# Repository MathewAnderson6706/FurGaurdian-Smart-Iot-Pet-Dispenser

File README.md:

# Automatic Pet Food Dispensor using RasperryPi 4 
Title Page (1st odd page not numbered, X.0 sections begin on odd pages, otherwise double sided and numbered)  
## Declaration of Joint Authorship   
### Task Distribution
We, FurGuardian, confirm that this breakdown of authorship represents my contribution to the work submitted for assessment and my contribution is my own work and  is expressed in my own words. Any uses made within the Technology Report of the works of any other author, separate to the work group, in any form (ideas, equations, figures, texts, tables, programs), are properly acknowledged at the point of use. A list of the references used is included.
| Task                  | Mathew | Justin | Tevadi | Zane |
|-----------------------|--------|--------|--------|------|
| **3D Print / Container**   | 50%   | 10%   | 10%   | 30%  |
| **Mobile Programming**     | 30%   | 50%   | 10%   | 10%  |
| **Hardware Connectivity**  | 45%   | 25%   | 15%   | 15%  |
| **Hardware Programming**   | 40%   | 40%   | 10%   | 10%  |
| **Documentation**          | 25%   | 25%   | 25%   | 25%  |

[^1]
[^1]: Technology Report Guidelines. OACETT, Revised September 2022. Available at: https://www.oacett.org/getmedia/5ad707d7-f472-4b24-a7fe-f34e270b0c41/2022_TR_Guidelines_-_Updated_Version_-_Sept_2022.pdf
## Proposal/Project Specifications   
[Link to proposal](wk01proposal.md).   
## Executive Summary   
Our project focuses on enhancing pet care for owners who are away during the day. It features a **smart pet food dispenser** equipped with advanced functionalities:

- **Camera**:  
  Allow owners to interact with their pets remotely, ensuring constant connection and engagement.

- **Infrared Sensor**:  
  Detects pet presence to automate feeding and interaction processes.

- **Stepper Motor**:  
  Dispenses precise portions of food to maintain proper dietary control.

- **solenoid push intermittent**:  
  Enables treat dispensing as an added feature for rewarding and engaging pets.

## Table of Contents

[Declaration of Joint Authorship](#declaration-of-joint-authorship)   
[Proposal/Project Specifications](#proposalproject-specifications)   
[Executive Summary](#executive-summary)   
[Table of Contents](#table-of-contents)   
[List of Figures](#list-of-figures)   

[1.0 Introduction](#10-introduction)   
[1.1 Background](#11-background)   
[1.2 Project Requirements and Specifications](#12-project-requirements-and-specifications)   
[1.3 Project Schedule](#13-project-schedule)   

[2.0 Hardware Development Platform Report/Build Instructions](#20-hardware-development-platform-reportbuild-instructions)  
[2.1 Mathew Anderson-Saavedra/A](#21-student-onea)  
[2.2 Tevadi Brookes/B](#22-student-twob)  
[2.3 Zane Aransevia/C](#23-student-threec)  
[2.4 Justin Chipman/D](#24-student-fourd)  

[3.0 Mobile Application Report](#30-mobile-application-report)  
[3.1 Deliverable 1](https://github.com/Chipman8472/FurGuardian/blob/master/Docs/FurGuardian_Deliverable1_Group8.pdf)  
[3.2 Deliverable 2](https://github.com/Chipman8472/FurGuardian/blob/master/Docs/Deliverable2/FurGuardian_PetWellness_Group8_2.pdf)  
[3.3 Deliverable 3](https://github.com/Chipman8472/FurGuardian/blob/master/Docs/FurGuardian_Deliverable3_Group8.pdf)  
[3.4 Deliverable 4](https://github.com/Chipman8472/FurGuardian/blob/master/Docs/FurGuardian_PetWellness_Deliverable4_Group8.pdf)   
[3.5 Deliverable 5](https://github.com/Chipman8472/FurGuardian/blob/master/Docs/Deliverable%205/FurGuardian_Deliverable5_Group8.pdf)  

[4.0 Integration](#40-integration)  
[4.1 Enterprise Wireless Connectivity](#41-enterprise-wireless-connectivity)  
[4.2 Database Configuration](#42-database-configuration)  
[4.3 Network and Security Considerations](#43-network-and-security-considerations)  
[4.4 Unit Testing](#44-unit-testing)  
[4.5 Production Testing](#45-production-testing)  
[4.6 Sustainability Considerations](#46-sustainability-considerations)  
[4.7 Challenges/Problems](#47-challengesproblems)  
[4.8 Solutions](#48-solutions)  

[5.0 Results and Discussion](#50-results-and-discussion)

[6.0 Conclusions](#60-conclusions)

[7.0 Appendix](#70-appendix)  
[7.1 Firmware Code](#71-firmware-code)  
[7.2 Mobile Application Code](#72-mobile-application-code)  

[8.0 References](#80-references)  

## List of Figures   
[Figure 1: Gantt Chart](#figure-1-gantt-chart)  

## 1.0 Introduction   
This project was undertaken to complete Humber Polytechnics CENG-355 Captsone project. The problem we are trying to solve is pet owners being away from their animals and not being able to interact or tend to thier needs while away. This dispensor aims to allow users to both interact with and feed thier pets while away from home. 

In section 1 we will discuss similar products on the market, the project requirements and specifications and the project schedule. In section 2 we will discuss the hardware devevlopment of the project. Section 3 links several reports about the development of the mobile app. Section 4 outlines the integration of the project as a whole.
### 1.1 Background
There are a few players on the market already for pet food dispenosrs. Pet Cube offers good remote pet interaction to keep pets engaged but lacks health information for the animals. Whistle offers good health tracking but lacks remote interaction with the animals. Our product aism to fuze these 2 functions into a single product.
### 1.2 Project Requirements and Specifications
This project has the following requirements.

Hardware:
- Raspberrypi 4
- Infared Sensor
- Solenoid push intermittent
- Stepper motor and a controller
- Camera

Firmware:
- Python dependencies (time, threading, cv2, smbus2, socket, RPI.GPIO, flask, pyrebase, pyngrok)
- Compatable python version

### 1.3 Project Schedule       
###### Figure 1: Gantt Chart     

## 2.0 Hardware Development Platform Report/Build Instructions   
### 2.1 Mathew Anderson-Saavedra/A
[Hardware report](hardware/ceng317reportMathew.md)   
### 2.2 Tevadi Brookes/B   
[Hardware report](hardware/ceng317reportTB.md)   
### 2.3 Zane Aransevia/C   
[Hardware report](hardware/rc522.md)  
### 2.4 Justin Chipman/D   
[Hardware report](hardware/ceng317report.md)   
  
## 3.0 Mobile Application Report   
### 3.1 Deliverable 1
[Mobile Deliverable 1](/tree/main/docs/Deliverable%201)   
### 3.2 Deliverable 2      
[Mobile Deliverable 2](/tree/main/docs/Deliverable%202)   
### 3.3 Deliverable 3      
[Mobile Deliverable 3](/tree/main/docs/Deliverable%203)   
### 3.4 Deliverable 4      
[Mobile Deliverable 4](/tree/main/docs/Deliverable%204)   
### 3.4 Deliverable 5      
[Mobile Deliverable 5](/tree/main/docs/Deliverable%205)   

## 4.0 Integration   
This secion will outline the various parts of our project being integrated together.
### 4.1 Enterprise Wireless Connectivity   
### 4.2 Database Configuration   
Our database is a realtime database using Firebase. We use the database to store feeding schedules, pet documents, login credentials, and remote connection URLs. The feeding schedules is fetched and stored locally on the Raspberrypi only being updated when the database signals there is a change. This allows the dispensor to still function without wifi if there is an outage. The pet documents are stored via the app for so the user has a one stop location for all its pets important information. The login credentials are stored in the database so that individual user data does not overlap and it can support more than one user.
### 4.3 Network and Security Considerations   
In this version of the project we are using a tunneling method to tie the raspberrypi's local ip on port 5000 to a public URL so that it can be accesses over other networks. In a production version I would ideally shift to a secure sever so that the feed is less accessable to the public. 

The passwords of the users are not stored in plain text in case of breaches. In future possible encrypting the email would increase security. 
### 4.4 Unit Testing   

### 4.5 Production Testing   
### 4.6 Sustainability Considerations
The controllers of the solenoid and the stepper motor require thier own individual power supply so they are supplied by either a battery or a seperate power adapter. This is not convinient and requires more powers sources than neccessary. 

A suggestion for future improvement would be creating a seperate PCB that can power all components with one adapter, this would make the project more sustainable.
### 4.7 Challenges/Problems   
- A major issue we had was getting the remote connection to be available accress other networks. 
### 4.8 Solutions   
- We created a tunneling method to allow the connection to be more available.
## 5.0 Results and Discussion   

## 6.0 Conclusions   

## 7.0 Appendix
### 7.1 Firmware Code   
[Link to firmware](hardware/firmware).
### 7.2 Mobile Application Code   
[Link to GitHub repository for app]()

## 8.0 References   
[COM-15093 Datasheet](https://mm.digikey.com/Volume0/opasdata/d220001/medias/docus/306/COM-15093_Web.pdf)

[ROB-11015 Datasheet](https://cdn.sparkfun.com/datasheets/Robotics/ZHO-0420S-05A4.5%20SPECIFICATION.pdf)

[Qwiic Relay Python Library](https://github.com/sparkfun/qwiic_relay_py/tree/main)

[AK9753 Datasheet](https://cdn.sparkfun.com/assets/6/7/9/8/e/AK9753_DS.pdf)

[sumbus2 Library](https://github.com/kplindegaard/smbus2)

[Qwiic_Human_Presence_Sensor_Breakout_AK9753 Github](https://github.com/sparkfun/Qwiic_Human_Presence_Sensor_Breakout_AK9753)

[Qwicc Motor Driver Guide](https://learn.sparkfun.com/tutorials/hookup-guide-for-the-qwiic-motor-driver#troubleshooting)

[Qwicc Motor Driver Python Library](https://github.com/sparkfun/Qwiic_SCMD_Py)

[Stepper Motor Datasheet](http://www.sparkfun.com/datasheets/Robotics/SM-42BYG011-25.pdf)

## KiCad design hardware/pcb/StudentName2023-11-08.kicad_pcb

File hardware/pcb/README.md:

# KiCad   
1. We will be designing a Raspberry Pi Interface board using [KiCad 8.0.3](https://downloads.kicad.org/kicad/windows/explore/stable/download/kicad-8.0.3-x86_64.exe).
2. Chapter 18 of the below textbook on pages 259-284, pages 268-293 of the pdf, has Project 2: Design a small Raspberry Pi HAT.
   Dalmaris, Peter. (2018). KiCad Like a Pro 2nd edition. United Kingdom: Elektor International Media B.V. Tech Explorations: EBOOK SOLO 978-1-64440-886-5. Note that newer versions of the textbook do not include the Design a small Raspberry Pi HAT project.   
3. Launch KiCad:   

4. Start with default settings:   

5. I have followed [Using a template](https://techexplorations.com/guides/kicad/3e/create-a-new-kicad-project-from-a-template/) and [Vlad's guide to PCB facilities in J233](PCBPrototypes.md) to a certain extent in order to create the below files to start from:
-   [Project File](/hardware/pcb/StudentName2023-11-08.kicad_pro)
-   [Schematic File](/hardware/pcb/StudentName2023-11-08.kicad_sch)
-   [PCB File](/hardware/pcb/StudentName2023-11-08.kicad_pcb)   
6. Download the above /hardware/pcb/StudentName2023-11-08.kicad_pro, pcb, and sch.
7. Use KiCad to open the _pro project file, then navigate to opening the PCB file.
8. Change the board in the PCB view to have your name and the current date.
9. If not routed already, route the BJT as a switch circuit (Section 4.5 Page 192 in your Electronic Devices by Floyd) traces on the PCB. This involves a 2N4124 NPN transistor with a 2.2 kOhm resistor between pin 11 -- GPIO17 and the base of the transistor, connect the emitter to the ground, and connect an LED with a series 220 Ohm resistor on the collector side to 3.3V. To do this:   
   - Click on the the end of say a resistor and press 'x' on the keyboard.
   - Then click on the other terminal that it should be connected to.
   - Consider ease of soldering.
10. Add a PinHeader_1x03_P2.54mm_Horizontal near the edge of the board to be able to connect a micro servo to pin 33 -- GPIO13, 3.3V (middle pin), and GND.
11. Add an extra Conn_01x08_Female that makes it possible to connect to the signals that we use for I2C (3V3,GND,SDA,SCL), the LED (GPIO17), a possible micro servo (GPIO13), and 2 extra connections.
12. Consider widening the traces where possible to reduce the likelihood of lifted pads/traces.   
13. Save "project as" what you changed the name and date to.   
14. Use File->fabrication outputs->Gerbers (.gbr)... to Plot the Gerbers   
15. also "Generate Drill Files"->PTH and NPTH in single file   
16. Save project
17. Use the Gerber Viewer to preview:
    1. F_Cu.gtl
    2. B_Cu.gbl
    3. F_Silkscreen.gto
    4. B_Silkscreen.gbo
    5. F_Mask.gts
    6. B_Mask.gbs
    7. Edge_Cuts.gm1
    8. .drl    
18. Upload your work in a zip file to your /hardware/pcb/ folder in the PrototypeZone organisation. The name of the zip should be in the format of your changed name and date (StudentName2023-09-24.zip) and it should contain the 3 KiCad files you worked on, the combined drill file, and the default Gerber plots as per the following list:   
    1. F.Cu   
    2. B.Cu   
    3. F.Silkscreen   
    4. B.Silkscreen   
    5. F.Mask   
    6. B.Mask   
    7. Edge.Cuts   
    8. The drill file   
    9. Your _pro file   
    10. Your _sch file   
    11. Your _pcb file
19. Once the professor knows that your zip file has been uploaded correctly they will send the class set to the lab next door to be made [in house](/hardware/pcb/PCBPrototypes.md).
20. When the completed PCB is available, proceed to [inspect it](/hardware/pcb/inspection.md).
21. Further iterations of the board can be made [in house](/hardware/pcb/PCBPrototypes.md) or by [OSHpark](https://oshpark.com/),  [MicroArt](https://microart.pcborders.com/), [Bittele](https://onlinequote.7pcb.com/), [JLC](https://jlcpcb.com/), [PCBway](https://www.pcbway.com/QuickOrderOnline.aspx), [Seeedstudio](https://www.seeedstudio.com/fusion_pcb.html), or other alternatives.

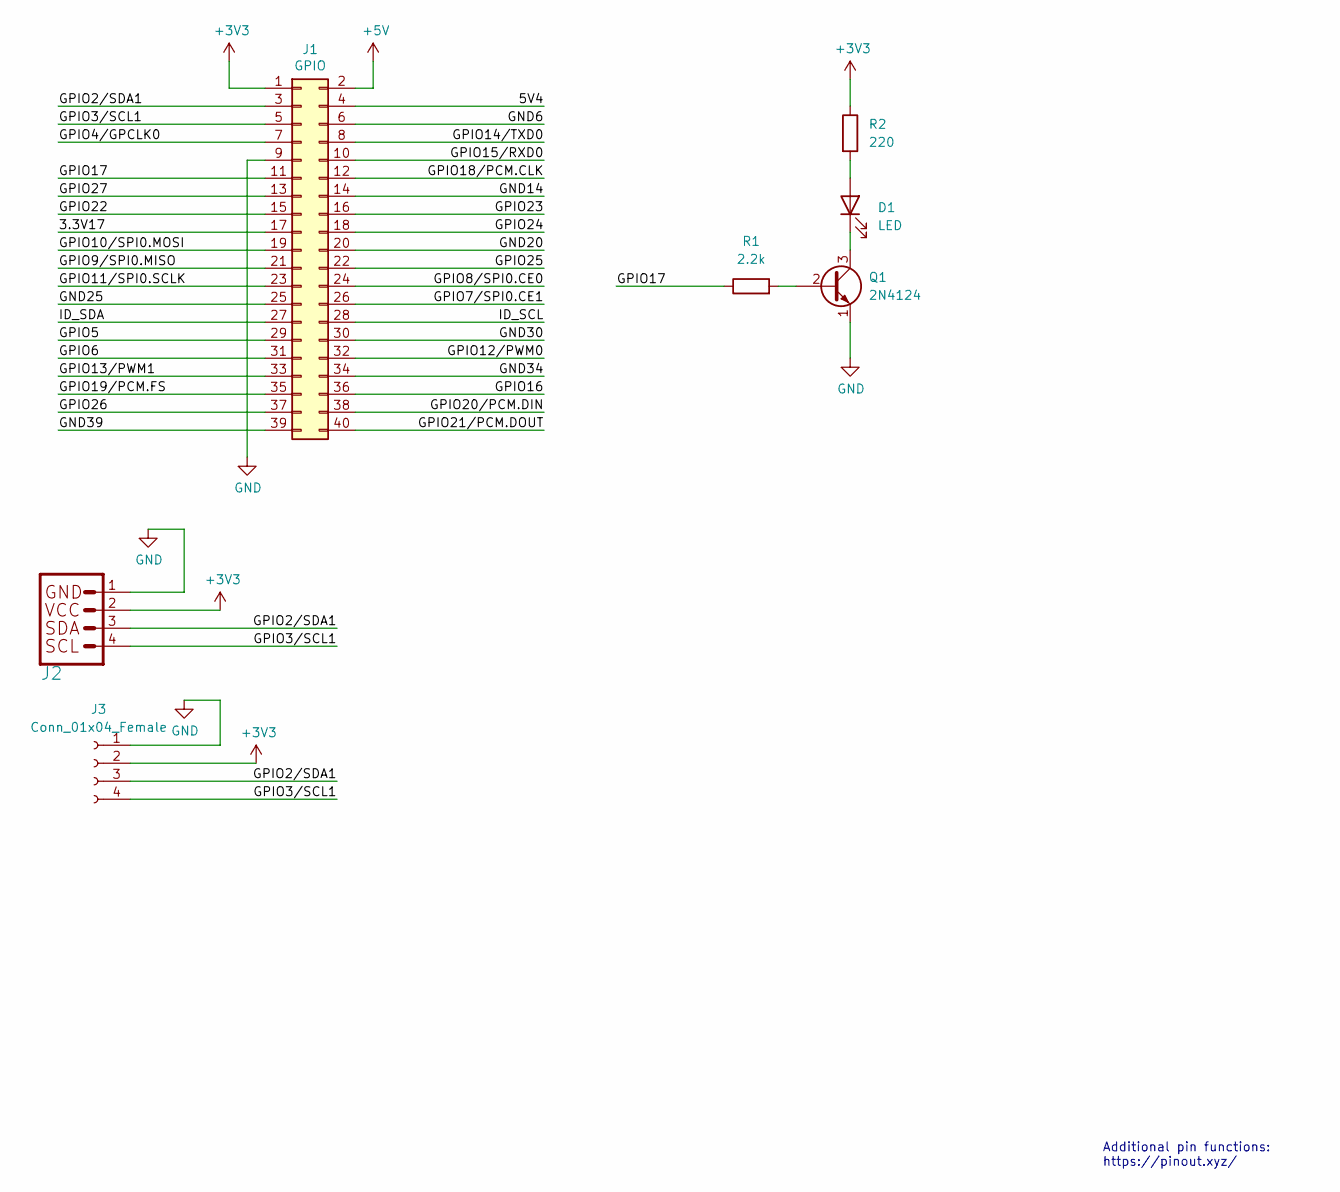
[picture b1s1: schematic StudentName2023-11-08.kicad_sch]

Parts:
D1: LED; LED_D5.0mm_Horizontal_O1.27mm_Z3.0mm
J1: GPIO; PinSocket_2x20_P2.54mm_Vertical
J2: Qwiic Right Angle; PinSocket_1x04_P2.00mm_Horizontal
J3: Conn_01x04_Female; PinSocket_1x04_P2.54mm_Horizontal
Q1: 2N4124; TO-92_Inline_Wide
R1: 2.2k; R_Axial_DIN0207_L6.3mm_D2.5mm_P15.24mm_Horizontal
R2: 220; R_Axial_DIN0207_L6.3mm_D2.5mm_P15.24mm_Horizontal

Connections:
+3V3: J1.1, J2.2, J3.2, R2.1
+5V: J1.2
/3.3V17: J1.17
/5V4: J1.4
/GND6: J1.6
/GND14: J1.14
/GND20: J1.20
/GND25: J1.25
/GND30: J1.30
/GND34: J1.34
/GND39: J1.39
/GPIO2/SDA1: J1.3, J2.3, J3.3
/GPIO3/SCL1: J1.5, J2.4, J3.4
/GPIO4/GPCLK0: J1.7
/GPIO5: J1.29
/GPIO6: J1.31
/GPIO7/SPI0.CE1: J1.26
/GPIO8/SPI0.CE0: J1.24
/GPIO9/SPI0.MISO: J1.21
/GPIO10/SPI0.MOSI: J1.19
/GPIO11/SPI0.SCLK: J1.23
/GPIO12/PWM0: J1.32
/GPIO13/PWM1: J1.33
/GPIO14/TXD0: J1.8
/GPIO15/RXD0: J1.10
/GPIO16: J1.36
/GPIO17: J1.11, R1.1
/GPIO18/PCM.CLK: J1.12
/GPIO19/PCM.FS: J1.35
/GPIO20/PCM.DIN: J1.38
/GPIO21/PCM.DOUT: J1.40
/GPIO22: J1.15
/GPIO23: J1.16
/GPIO24: J1.18
/GPIO25: J1.22
/GPIO26: J1.37
/GPIO27: J1.13
/ID_SCL: J1.28
/ID_SDA: J1.27
GND: J1.9, J2.1, J3.1, Q1.1 (E)
unnamed: D1.1 (K), Q1.3 (C)
unnamed: D1.2 (A), R2.2
unnamed: Q1.2 (B), R1.2

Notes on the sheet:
Additional pin functions: https://pinout.xyz/

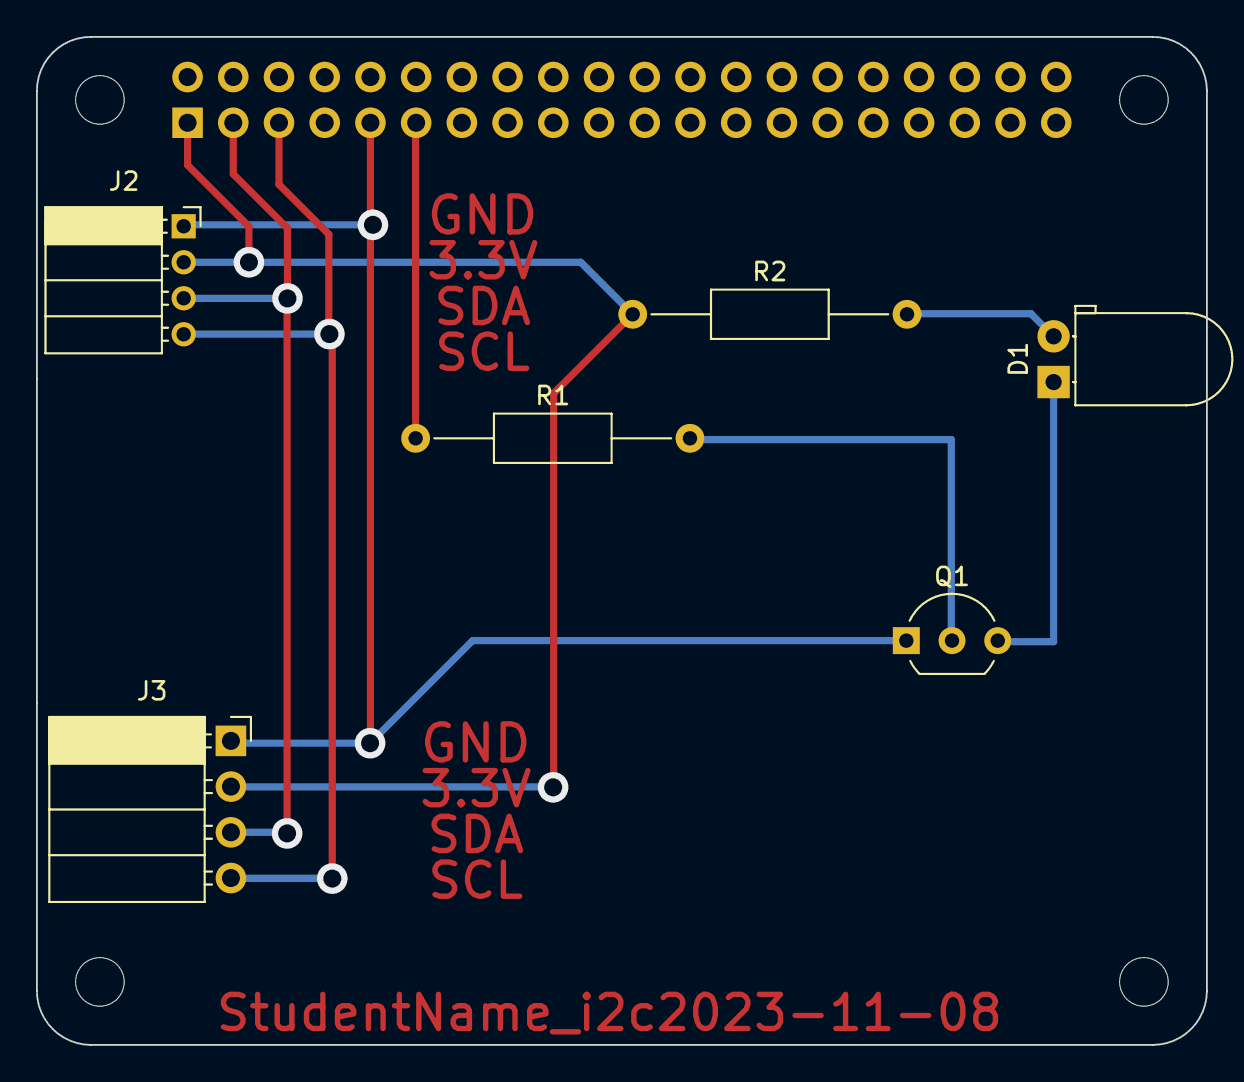
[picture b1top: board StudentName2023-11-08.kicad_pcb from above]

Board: 2 copper layers, 65.0 x 56.0 mm, 11 parts (1 on the bottom side), 8 nets.

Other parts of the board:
MH1, MH2, MH3, MH4: MountingHole_2.7mm_M2.5
